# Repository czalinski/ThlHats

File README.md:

# ThlHats

Test devices in the Raspberry Pi HAT form factor: KiCad 10 PCB designs and
their firmware (PIC, ESP32, STM32).

## Design rules

- 2-layer boards, at most 100 × 100 mm
- Mount on standard Raspberry Pi M2.5 standoffs (58 × 49 mm hole pattern)
- All symbols, footprints and 3D models are kept in this repo under `lib/`.
  The KiCad projects do not use the stock or globally installed libraries.

## Requirements

- KiCad 10 (`kicad-cli` and the `pcbnew` Python module, run with the system `python3`)
- `pdftoppm` (poppler-utils), optional, for rendering schematics to images

## Quick start

```sh
# New 65 x 56.5 mm HAT with the 40-pin header, M2.5 holes, and a GND pour
tools/new_board.py my-board --title "My Board" --mcu esp32

# Bring parts into the repo libraries
tools/kilib.py symbol RF_Module:ESP32-S3-WROOM-1     # also copies footprint + 3D model
tools/kilib.py footprint Package_SO:SOIC-8_3.9x4.9mm_P1.27mm

# Parts from SnapEDA / Ultra Librarian / vendors
tools/kilib.py symbol PART --from ~/Downloads/PART.kicad_sym --lib Thl_Sensor --source "SnapEDA"
tools/kilib.py footprint PART_FP --from ~/Downloads/PART.kicad_mod --model ~/Downloads/PART.step \
    --lib Thl_Sensor --source "SnapEDA"

# Check (house rules + ERC + DRC) and produce fab files
tools/check_board.py boards/my-board
tools/fab.py boards/my-board
```

Open `boards/<name>/hardware/<name>.kicad_pro` in KiCad. Its project library
tables list only the libraries in `lib/`. After you add a new library, run
`tools/kilib.py sync`. The import commands do this for you.

## Layout

| Path | Contents |
|------|----------|
| `lib/` | Symbols, footprints, 3D models, and `SOURCES.md` (where each part came from) |
| `boards/<name>/hardware/` | KiCad project |
| `boards/<name>/firmware/` | Firmware for that board |
| `docs/` | Requirements (`docs/requirements.md`) |
| `tools/` | Board generator, library importer, symbol generator, checker, fab-output script |

## Library licensing

Parts copied from the KiCad libraries are CC-BY-SA 4.0 with the KiCad library
exception: boards made with them are not affected by the license. Parts from
other sources keep their own licenses, which are recorded in `lib/SOURCES.md`.

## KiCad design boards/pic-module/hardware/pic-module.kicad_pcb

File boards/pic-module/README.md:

# PIC32MK + power module (POC #1)

Plug-in module for the proof-of-concept boards (docs/requirements.md 4.0): the
can-controller's MCU and power entry, hand-soldered once and moved between POC
boards.

- Board: 56 x 74 mm, 2 layers, rev A. No mounting holes (`board.json`).
- U1 PIC32MK1024MCM064-I/PT (TQFP-64), 12 MHz crystal, decoupling, AVDD bead,
  MCLR network, ICSP (J2, PICkit/Snap pinout), debug UART (J5), heartbeat LED
  on RD8. Crystal Y1: Abracon ABM3-12.000MHZ-B2-T (12 MHz, 5.0 x 3.2 mm,
  CL 18 pF, ESR 60 ohm max, -20 to 70 C) with 27 pF C0G load caps; same part
  for the final board.
- Power entry copied from can-controller: J20 12 V in, F20 4 A, reverse-polarity
  P-FET Q1, TVS D31, TRACO TDN 5-2411WI (U20, isolated, 5 V 1 A), MCP1826S 3.3 V
  LDO (U2, 1 A).
- Two domains: RACK (+12V, GND_RACK) on the top strip, LOGIC (+5V, +3V3, GND,
  floating) below. U20 is the only crossing; a 2 mm copper-free gap separates
  them on both layers.

## Host interface

J3/J4 are 2 x 20, 2.54 mm sockets on the module's **bottom** (Sullins
PPTC202LFBN-RC, or any 2.54 mm stock); the host carries pin headers (Sullins
PRPC020DAAN-RC, or cut breakaway strip), via
the library part `Thl_Module:PIC32MK_Module` / footprint
`Thl_Module:PIC32MK_Module_Host` (origin = module top-left corner).

Keying:
1. J4 is placed so that a module turned 180 degrees lands 1.24 mm (half a pitch)
   off the host pins.
2. J3.9 is blocked on the module (glue a cut-off pin into that socket
   position); the host has no pin there. J3.10 is unused on both sides: it
   spaces the RACK pins from the LOGIC pins.

Pull pins 9 and 10 (row 5 of header A) out of the host's header before
soldering it; the host footprint has no pads there.

The pinout is generated: `hardware/module_pinout.py` matches the MCU pins to
header positions clockwise around the chip, so the module's fan-out has no
crossings. Host pin names are the PIC port names; a suffix says what the
module itself hangs on that pin:

- `RB5_PGD`, `RB6_PGC`: ICSP (J2). Keep host loads off them, or isolate them
  while programming.
- `RF1_TX`, `RC6_RX`: debug UART J5 (U1TX/U1RX by PPS).
- `RD8_LED`: heartbeat LED D2 (1 k to GND through the LED).
- `MCLR`: 10 k pull-up and 100 nF on the module; a host may add a reset button.
- `USB_DP`, `USB_DN`, `VBUS`: 100 k pull-downs on the module (USB unused unless
  a host wires a connector).

Supplies on the header: +12V x4 and GND_RACK x4 (J3.1-8, RACK, after the
input protection; a host may feed +12V here instead of using J20, without
protection), +5V x3, +3V3 x5, GND x11 (LOGIC). +5V is limited by U20 (1 A
total, of which the module uses about 0.1 A); +3V3 by U2 (1 A, mind the LDO's
dissipation: (5 - 3.3) V x I).

| J3 odd | J3 even | | J4 odd | J4 even |
|---|---|---|---|---|
| 1 +12V | 2 +12V | | 1 +5V | 2 GND |
| 3 +12V | 4 +12V | | 3 RG9 | 4 MCLR |
| 5 GND_RACK | 6 GND_RACK | | 5 RG8 | 6 RG7 |
| 7 GND_RACK | 8 GND_RACK | | 7 RG6 | 8 RB15 |
| 9 (key: no pin) | 10 (no pin) | | 9 +3V3 | 10 GND |
| 11 GND | 12 GND | | 11 RB14 | 12 RA7 |
| 13 RA12 | 14 RA11 | | 13 RA10 | 14 RB13 |
| 15 RA0 | 16 RA1 | | 15 RB12 | 16 RB11 |
| 17 RB0 | 18 RB1 | | 17 RB10 | 18 RF1_TX |
| 19 +3V3 | 20 GND | | 19 +3V3 | 20 GND |
| 21 RB2 | 22 RB3 | | 21 RF0 | 22 RC9 |
| 23 RC0 | 24 RC1 | | 23 RD6 | 24 RD5 |
| 25 RC2 | 26 RC11 | | 25 RC8 | 26 RC7 |
| 27 +5V | 28 GND | | 27 RC6_RX | 28 RB9 |
| 29 RE12 | 30 RE13 | | 29 +5V | 30 GND |
| 31 RE14 | 32 RE15 | | 31 RB8 | 32 RC13 |
| 33 RA8 | 34 RB4 | | 33 RB7 | 34 RC10 |
| 35 +3V3 | 36 GND | | 35 RB6_PGC | 36 RB5_PGD |
| 37 RA4 | 38 USB_DP | | 37 RD8_LED | 38 VBUS |
| 39 USB_DN | 40 GND | | 39 +3V3 | 40 GND |

## Changing the pinout

Edit `hardware/module_pinout.py`, then regenerate the module
(`gen_schematic.py`, `tools/sync_pcb.py`, `place.py`, reroute) and the host
part (`python3 lib/footprint_src/Thl_Module/pic_module.py` and
`tools/make_symbol.py lib/symbol_src/Thl_Module/PIC32MK_Module.csv`), and
update every host board.

## Build files

- `hardware/gen_schematic.py`: schematic (bootstrap; stop using it once the
  schematic is edited in KiCad).
- `hardware/place.py`: outline, placement, pours (GND both layers in LOGIC,
  GND_RACK / +12V in RACK, a +3V3 island under U1), isolation gap keep-outs
  (rerunnable; leaves tracks alone).
- `hardware/route.py`: pre-routing (not rerunnable): U1 VDD pins get inward
  stubs into the +3V3 island, VSS pins inward vias to the GND plane, every
  other SMD ground pad a fanout via.
- Autorouting: `tools/freeroute.py` (Freerouting 1.9.0 under xvfb, top layer
  preferred, bottom = GND plane), command in `route.py`'s docstring.
- Rev A was then finished by hand (2026-10-06): `miniroute.complete_net` for
  the last few nets, AVDD (U1.19) escaped inward to a via, RC11 kept on top
  past J3, `miniroute.stitch_pads` for header GND pins cut off from the pour,
  `tools/silk_tidy.py` for the references. Rerunning `place.py` is safe;
  rerunning `route.py`/the autorouter starts over and loses those fixes.
- U20 (TRACO: no traces under the converter) is enforced by a rule in
  `pic-module.kicad_dru`: only its own nets under its courtyard.
- Board setup accepts one thermal spoke (`min_resolved_spokes` 1): header GND
  pins between fan-out tracks often get only one.

## Open items

- Verify the Sullins socket/header MPNs (or use stock 2.54 mm parts) and the
  mated height against parts under the module on the host.
- No STEP models for U20 (TRACO TDN 5WI) and F20 (NANO2 fuse).

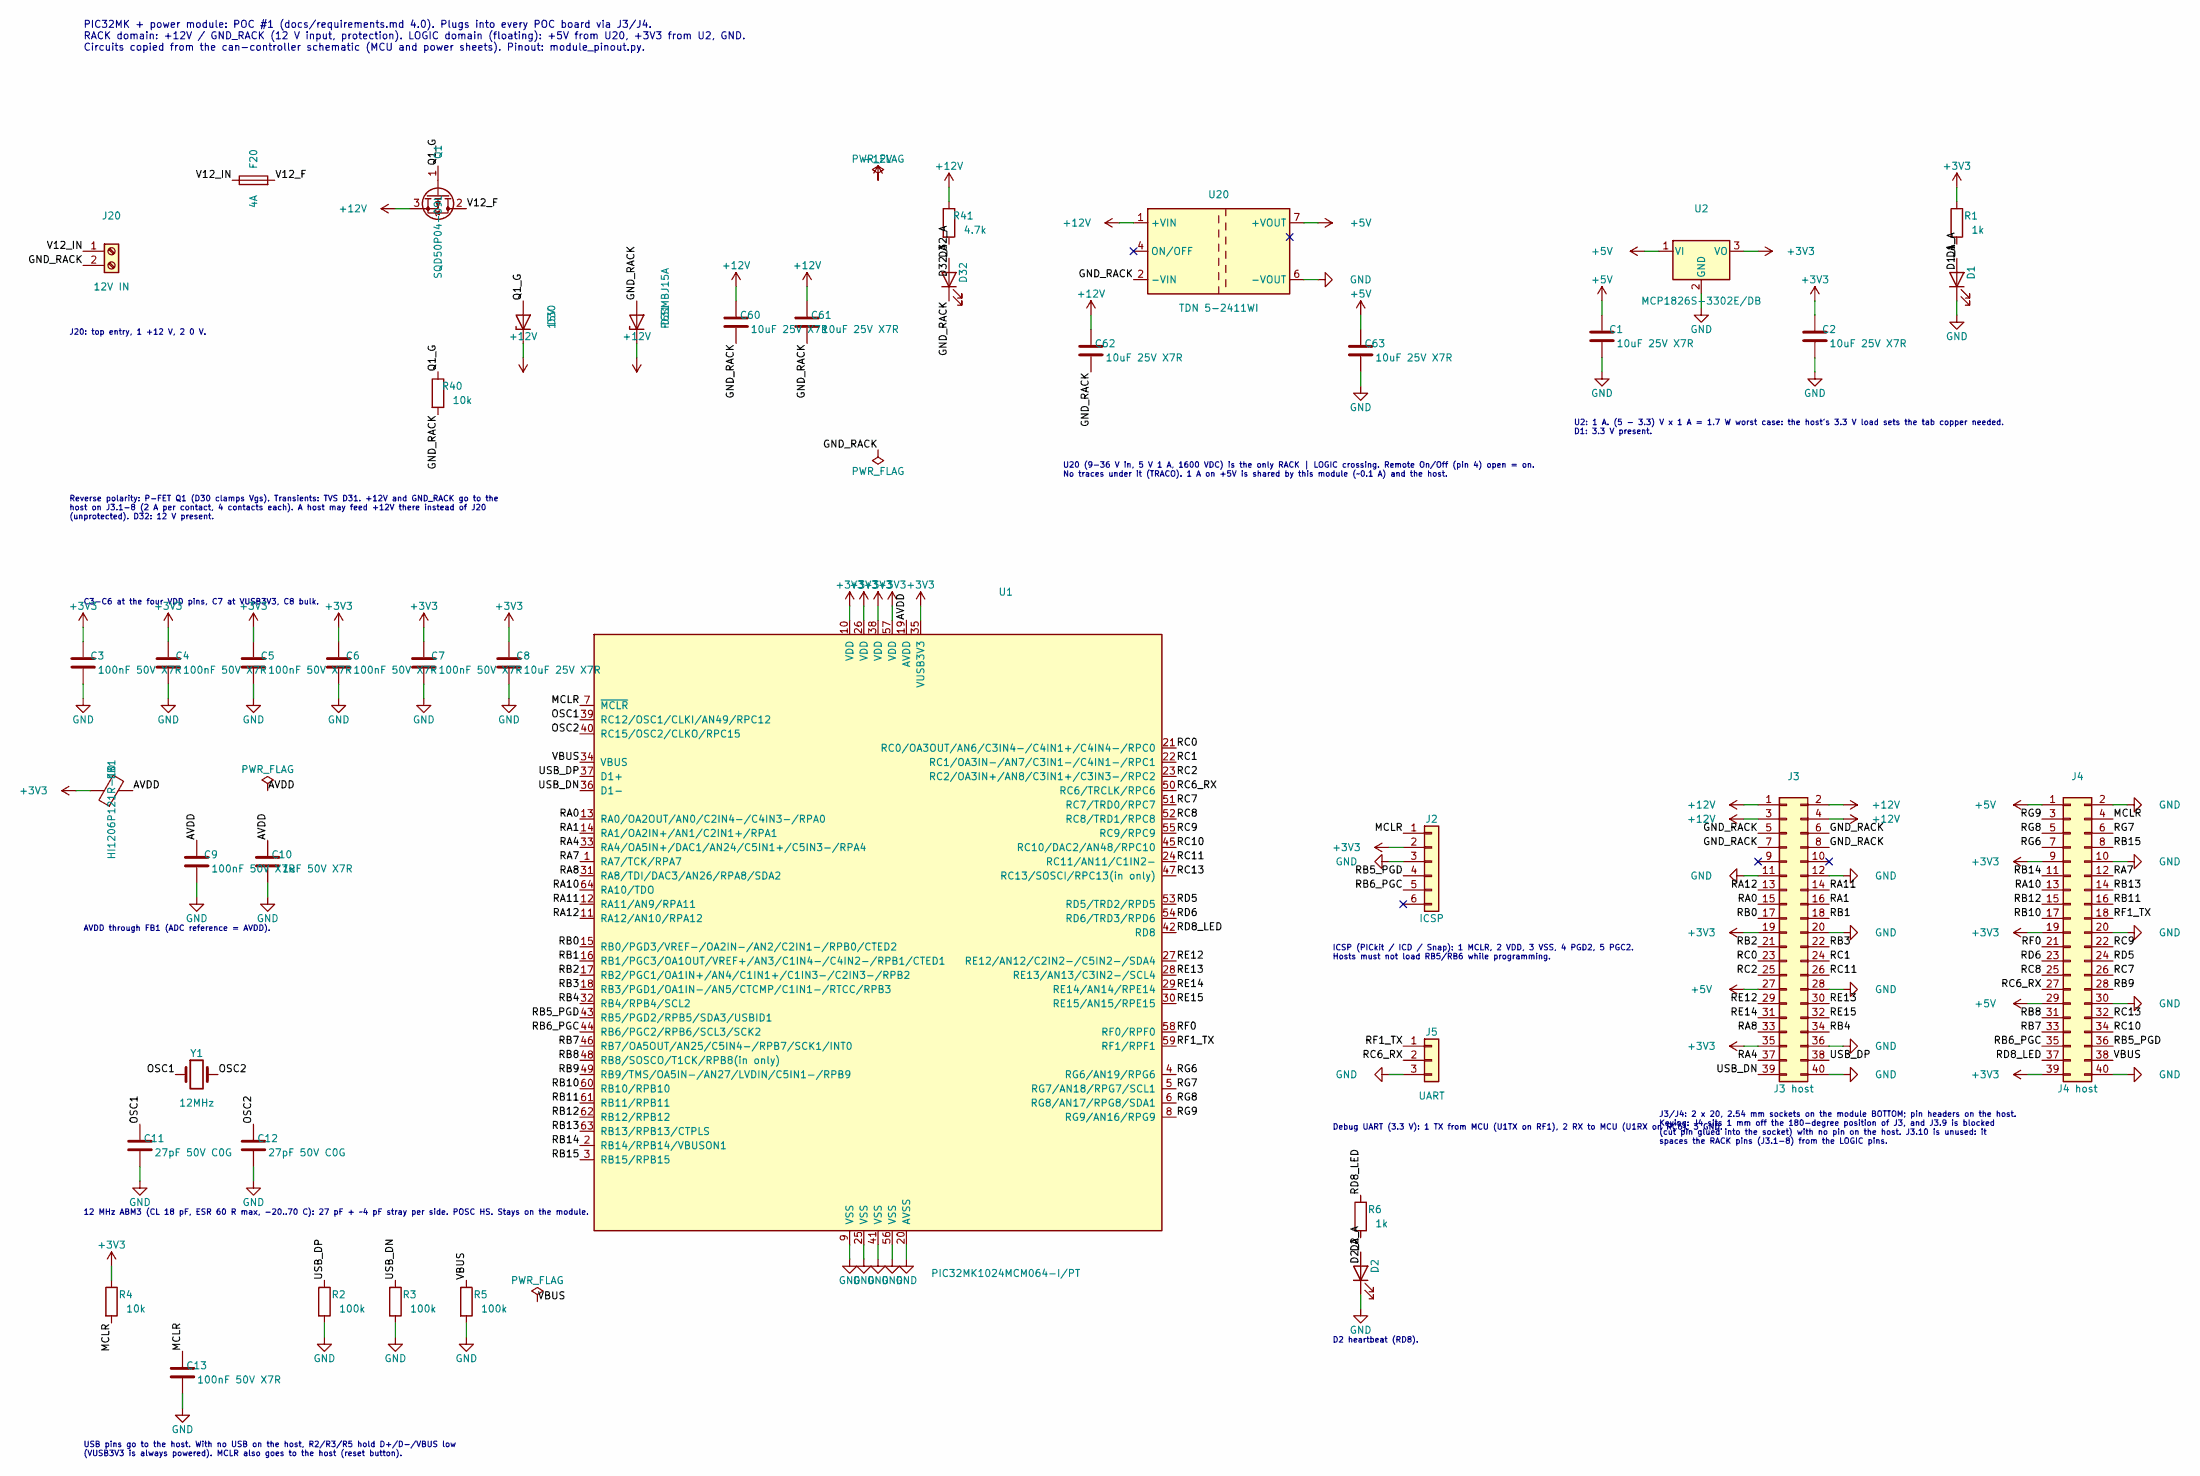
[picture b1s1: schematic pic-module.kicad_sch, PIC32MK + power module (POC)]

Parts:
C1, C2, C8, C60, C61, C62, C63: 10uF 25V X7R; C_1206_3216Metric_Pad1.33x1.80mm_HandSolder; MPN CL31B106KAHZW6E
C3, C4, C5, C6, C7, C9, C13: 100nF 50V X7R; C_0805_2012Metric_Pad1.18x1.45mm_HandSolder; MPN C0805C104K5RACTU
C10: 1uF 50V X7R; C_1206_3216Metric_Pad1.33x1.80mm_HandSolder; MPN C1206C105K5RACTU
C11, C12: 27pF 50V C0G; C_0805_2012Metric_Pad1.18x1.45mm_HandSolder; MPN C0805C270J5GACTU
D1, D2, D32: LED green; LED_1206_3216Metric_Pad1.42x1.75mm_HandSolder; MPN LTST-C150KGKT
D30: 15V; D_SOD-123; MPN BZT52C15-7-F
D31: P6SMBJ15A; D_SMB_Handsoldering; MPN P6SMBJ15A
F20: 4A; Fuse_Littelfuse-NANO2-451_453; MPN 0451004.MRL
FB1: HI1206P121R-10; L_1206_3216Metric_Pad1.22x1.90mm_HandSolder; MPN HI1206P121R-10
J2: ICSP; PinHeader_1x06_P2.54mm_Vertical; MPN TSW-106-07-G-S
J3: J3 host; PinSocket_2x20_P2.54mm_Vertical; MPN PPTC202LFBN-RC
J4: J4 host; PinSocket_2x20_P2.54mm_Vertical; MPN PPTC202LFBN-RC
J5: UART; PinHeader_1x03_P2.54mm_Vertical; MPN TSW-103-07-G-S
J20: 12V IN; PhoenixContact_MSTBVA_2,5_2-G-5,08_1x02_P5.08mm_Vertical; MPN 1755736
Q1: SQD50P04-09L; TO-252-2; MPN SQD50P04-09L_GE3
R1, R6: 1k; R_1206_3216Metric_Pad1.30x1.75mm_HandSolder; MPN RC1206FR-071KL
R2, R3, R5: 100k; R_1206_3216Metric_Pad1.30x1.75mm_HandSolder; MPN RC1206FR-07100KL
R4, R40: 10k; R_1206_3216Metric_Pad1.30x1.75mm_HandSolder; MPN RC1206FR-0710KL
R41: 4.7k; R_1206_3216Metric_Pad1.30x1.75mm_HandSolder; MPN RC1206FR-074K7L
U1: PIC32MK1024MCM064-I/PT; TQFP-64_10x10mm_P0.5mm; MPN PIC32MK1024MCM064-I/PT
U2: MCP1826S-3302E/DB; SOT-223-3_TabPin2; MPN MCP1826S-3302E/DB
U20: TDN 5-2411WI; Converter_DCDC_TRACO_TDN_5-xxxxWI_THT; MPN TDN 5-2411WI
Y1: 12MHz; Crystal_SMD_5032-2Pin_5.0x3.2mm_HandSoldering; MPN ABM3-12.000MHZ-B2-T

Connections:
+3V3: C2.1, C3.1, C4.1, C5.1, C6.1, C7.1, C8.1, FB1.1, J2.2, J3.19, J3.35, J4.9, J4.19, J4.39, R1.1, R4.1, U1.10 (VDD), U1.26 (VDD), U1.35 (VUSB3V3), U1.38 (VDD), U1.57 (VDD), U2.3 (VO)
+5V: C1.1, C63.1, J3.27, J4.1, J4.29, U2.1 (VI), U20.7 (+VOUT)
+12V: C60.1, C61.1, C62.1, D30.1 (K), D31.1 (K), J3.1, J3.2, J3.3, J3.4, Q1.3 (S), R41.1, U20.1 (+VIN)
/AVDD: C9.1, C10.1, FB1.2, U1.19 (AVDD)
/D1_A: D1.2 (A), R1.2
/D2_A: D2.2 (A), R6.2
/D32_A: D32.2 (A), R41.2
/GND_RACK: C60.2, C61.2, C62.2, D31.2 (A), D32.1 (K), J3.5, J3.6, J3.7, J3.8, J20.2, R40.2, U20.2 (-VIN)
/MCLR: C13.1, J2.1, J4.4, R4.2, U1.7 (~MCLR)
/OSC1: C11.1, U1.39 (RC12/OSC1/CLKI/AN49/RPC12), Y1.1
/OSC2: C12.1, U1.40 (RC15/OSC2/CLKO/RPC15), Y1.2
/Q1_G: D30.2 (A), Q1.1 (G), R40.1
/RA0: J3.15, U1.13 (RA0/OA2OUT/AN0/C2IN4-/C4IN3-/RPA0)
/RA1: J3.16, U1.14 (RA1/OA2IN+/AN1/C2IN1+/RPA1)
/RA4: J3.37, U1.33 (RA4/OA5IN+/DAC1/AN24/C5IN1+/C5IN3-/RPA4)
/RA7: J4.12, U1.1 (RA7/TCK/RPA7)
/RA8: J3.33, U1.31 (RA8/TDI/DAC3/AN26/RPA8/SDA2)
/RA10: J4.13, U1.64 (RA10/TDO)
/RA11: J3.14, U1.12 (RA11/AN9/RPA11)
/RA12: J3.13, U1.11 (RA12/AN10/RPA12)
/RB0: J3.17, U1.15 (RB0/PGD3/VREF-/OA2IN-/AN2/C2IN1-/RPB0/C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)
/RB1: J3.18, U1.16 (RB1/PGC3/OA1OUT/VREF+/AN3/C1IN4-/C4IN2-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)
/RB2: J3.21, U1.17 (RB2/PGC1/OA1IN+/AN4/C1IN1+/C1IN3-/C2IN3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)
/RB3: J3.22, U1.18 (RB3/PGD1/OA1IN-/AN5/CTCMP/C1IN1-/RTCC/R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)
/RB4: J3.34, U1.32 (RB4/RPB4/SCL2)
/RB5_PGD: J2.4, J4.36, U1.43 (RB5/PGD2/RPB5/SDA3/USBID1)
/RB6_PGC: J2.5, J4.35, U1.44 (RB6/PGC2/RPB6/SCL3/SCK2)
/RB7: J4.33, U1.46 (RB7/OA5OUT/AN25/C5IN4-/RPB7/SCK1/INT0)
/RB8: J4.31, U1.48 (RB8/SOSCO/T1CK/RPB8(in only))
/RB9: J4.28, U1.49 (RB9/TMS/OA5IN-/AN27/LVDIN/C5IN1-/RPB9)
/RB10: J4.17, U1.60 (RB10/RPB10)
/RB11: J4.16, U1.61 (RB11/RPB11)
/RB12: J4.15, U1.62 (RB12/RPB12)
/RB13: J4.14, U1.63 (RB13/RPB13/CTPLS)
/RB14: J4.11, U1.2 (RB14/RPB14/VBUSON1)
/RB15: J4.8, U1.3 (RB15/RPB15)
/RC0: J3.23, U1.21 (RC0/OA3OUT/AN6/C3IN4-/C4IN1+/C4IN4-/RPC0)
/RC1: J3.24, U1.22 (RC1/OA3IN-/AN7/C3IN1-/C4IN1-/RPC1)
/RC2: J3.25, U1.23 (RC2/OA3IN+/AN8/C3IN1+/C3IN3-/RPC2)
/RC6_RX: J4.27, J5.2, U1.50 (RC6/TRCLK/RPC6)
/RC7: J4.26, U1.51 (RC7/TRD0/RPC7)
/RC8: J4.25, U1.52 (RC8/TRD1/RPC8)
/RC9: J4.22, U1.55 (RC9/RPC9)
/RC10: J4.34, U1.45 (RC10/DAC2/AN48/RPC10)
/RC11: J3.26, U1.24 (RC11/AN11/C1IN2-)
/RC13: J4.32, U1.47 (RC13/SOSCI/RPC13(in only))
/RD5: J4.24, U1.53 (RD5/TRD2/RPD5)
/RD6: J4.23, U1.54 (RD6/TRD3/RPD6)
/RD8_LED: J4.37, R6.1, U1.42 (RD8)
/RE12: J3.29, U1.27 (RE12/AN12/C2IN2-/C5IN2-/SDA4)
/RE13: J3.30, U1.28 (RE13/AN13/C3IN2-/SCL4)
/RE14: J3.31, U1.29 (RE14/AN14/RPE14)
/RE15: J3.32, U1.30 (RE15/AN15/RPE15)
/RF0: J4.21, U1.58 (RF0/RPF0)
/RF1_TX: J4.18, J5.1, U1.59 (RF1/RPF1)
/RG6: J4.7, U1.4 (RG6/AN19/RPG6)
/RG7: J4.6, U1.5 (RG7/AN18/RPG7/SCL1)
/RG8: J4.5, U1.6 (RG8/AN17/RPG8/SDA1)
/RG9: J4.3, U1.8 (RG9/AN16/RPG9)
/USB_DN: J3.39, R3.1, U1.36 (D1-)
/USB_DP: J3.38, R2.1, U1.37 (D1+)
/V12_F: F20.2, Q1.2 (D)
/V12_IN: F20.1, J20.1
/VBUS: J4.38, R5.1, U1.34 (VBUS)
GND: C1.2, C2.2, C3.2, C4.2, C5.2, C6.2, C7.2, C8.2, C9.2, C10.2, C11.2, C12.2, C13.2, C63.2, D1.1 (K), D2.1 (K), J2.3, J3.11, J3.12, J3.20, J3.28, J3.36, J3.40, J4.2, J4.10, J4.20, J4.30, J4.40, J5.3, R2.2, R3.2, R5.2, U1.9 (VSS), U1.20 (AVSS), U1.25 (VSS), U1.41 (VSS), U1.56 (VSS), U2.2 (GND), U20.6 (-VOUT)

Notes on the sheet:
PIC32MK + power module: POC #1 (docs/requirements.md 4.0). Plugs into every POC board via J3/J4. RACK domain: +12V / GND_RACK (12 V input, protection). LOGIC domain (floating): +5V from U20, +3V3 from U2, GND. Circuits copied from the can-controller schematic (MCU and power sheets). Pinout: module_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
J20: top entry, 1 +12 V, 2 0 V.
Reverse polarity: P-FET Q1 (D30 clamps Vgs). Transients: TVS D31. +12V and GND_RACK go to the host on J3.1-8 (2 A per contact, 4 contacts each). A host may feed +12V there instead of J20 (unprotected). D32: 12 V present.
U20 (9-36 V in, 5 V 1 A, 1600 VDC) is the only RACK | LOGIC crossing. Remote On/Off (pin 4) open = on. No traces under it (TRACO). 1 A on +5V is shared by this module (~0.1 A) and the host.
U2: 1 A. (5 - 3.3) V x 1 A = 1.7 W worst case: the host's 3.3 V load sets the tab copper needed. D1: 3.3 V present.
C3-C6 at the four VDD pins, C7 at VUSB3V3, C8 bulk.
AVDD through FB1 (ADC reference = AVDD).
12 MHz ABM3 (CL 18 pF, ESR 60 R max, -20..70 C): 27 pF + ~4 pF stray per side. POSC HS. Stays on the module.
USB pins go to the host. With no USB on the host, R2/R3/R5 hold D+/D-/VBUS low (VUSB3V3 is always powered). MCLR also goes to the host (reset button).
ICSP (PICkit / ICD / Snap): 1 MCLR, 2 VDD, 3 VSS, 4 PGD2, 5 PGC2. Hosts must not load RB5/RB6 while programming.
Debug UART (3.3 V): 1 TX from MCU (U1TX on RF1), 2 RX to MCU (U1RX on RC6), 3 GND.
D2 heartbeat (RD8).
J3/J4: 2 x 20, 2.54 mm sockets on the module BOTTOM; pin headers on the host. Keying: J4 sits 1 mm off the 180-degree position of J3, and J3.9 is blocked (cut pin glued into the socket) with no pin on the host. J3.10 is unused: it spaces the RACK pins (J3.1-8) from the LOGIC pins.

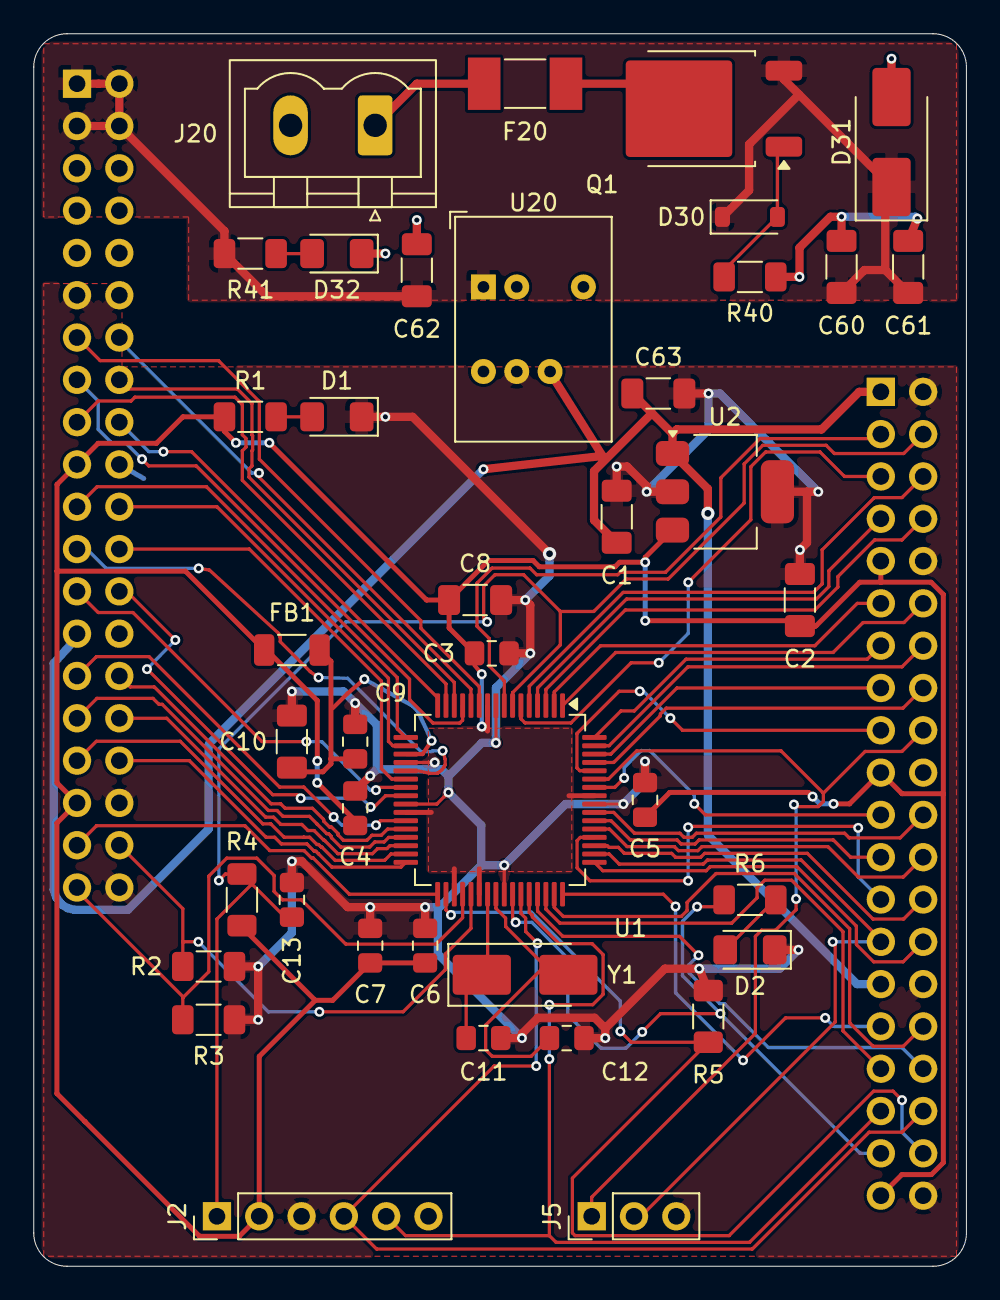
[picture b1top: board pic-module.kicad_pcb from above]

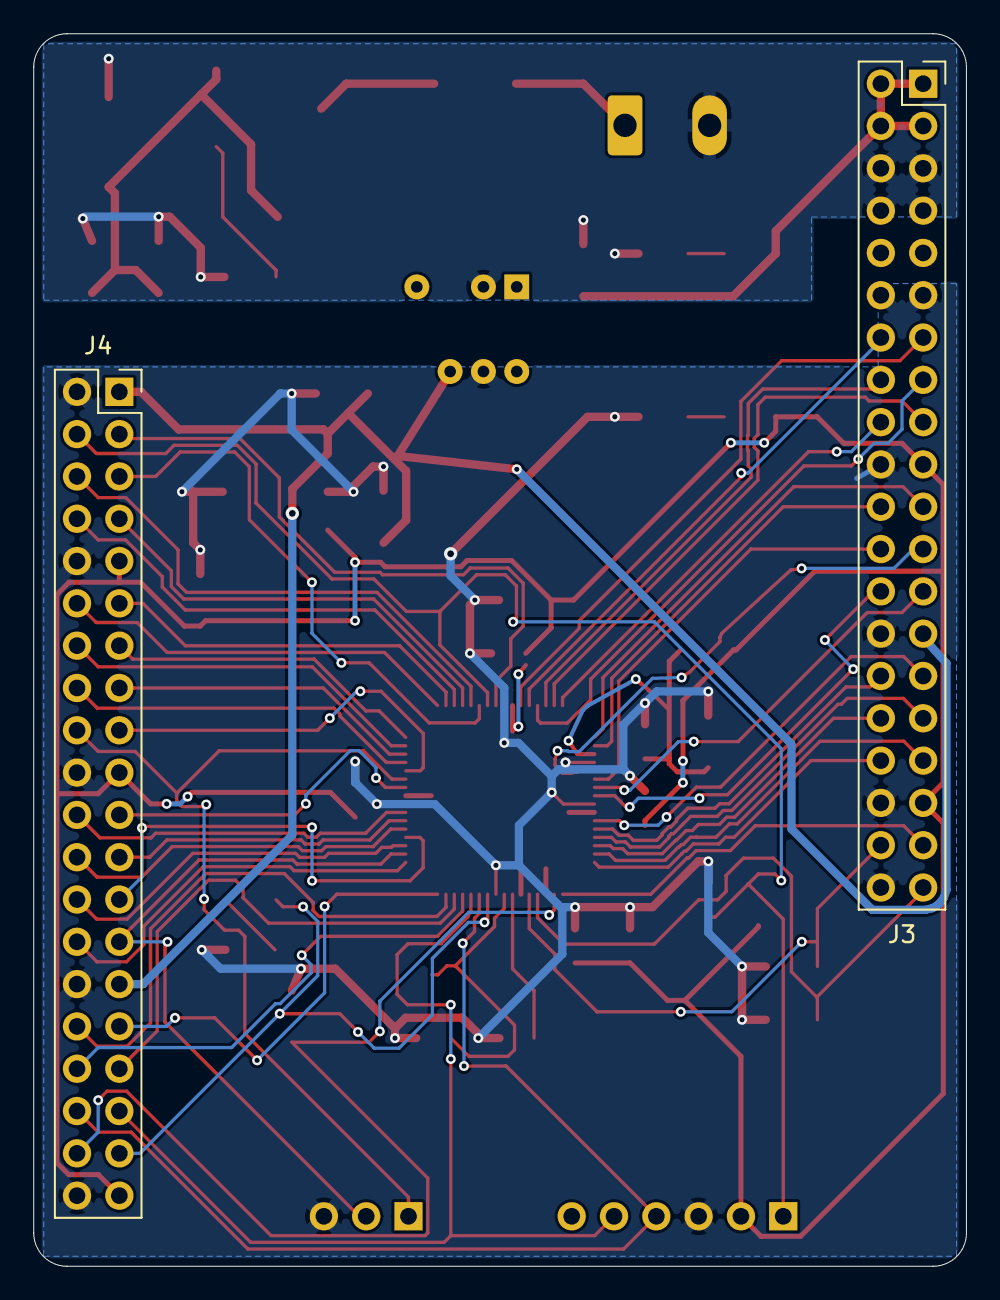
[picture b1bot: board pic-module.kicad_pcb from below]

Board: 2 copper layers, 56.0 x 74.0 mm, 42 parts (2 on the bottom side), 65 nets.

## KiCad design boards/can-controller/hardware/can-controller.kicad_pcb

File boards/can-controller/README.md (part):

# CAN Controller

Primary controller for the ThlHats HASS stack: four isolated CAN FD buses and
relay drive (the gaps the MCC HATs leave), plus a couple of GPIO and
high-voltage analog inputs so one card covers small jobs. Requirements:
[`docs/requirements.md`](../../docs/requirements.md), sections 3 and 4.1.

- Board: 100 x 100 mm, 2 layers, rev A
- Mounting: stack interface with can-ssr (requirements 4.4): 4 x M4 corner
  holes on a 91 x 91 mm square; base of a stack of up to 4 can-ssr. No Pi holes
- Host link: **Ethernet** (WIZnet W6100, user-space TCP/UDP sockets, no
  drivers or sudo on the host); a switch is assumed in the rack
- Power: one 12 V DIN supply; the logic runs from an isolated DC-DC
- MCU: PIC32MK1024MCM064-I/PT; firmware loads over the ICSP header

## Scope reduction (2026-10-06)

The rev 3 design (8 GPIO, 8 relays through ISO6740 isolators, a ULN2803A and
an MCP23008 expander, 4 AI on an MCP3428, 2 x 0-10 V AO with DAC, reference,
LM358B and a 13 V boost) had grown past the board's purpose. Cut: analog out
(MCC 152 / can-ssr cover it), the expander, the isolators and ULN, 24 V-tolerant
GPIO, and half of the GPIO, relay and AI channels. Later the same day: USB and
the Pi header gave way to Ethernet, and every CAN bus got its own isolation
(no assumptions about DUT grounds). The schematic, placement and routing in
the "Superseded" sections are from the old scope and will be redone;
`gen_schematic.py`, `place_board.py` and `place_rev3.py` describe it.

## Domains and functional blocks

| Block | Baseline parts | Domain |
|-------|----------------|--------|
| MCU | PIC32MK1024MCM064, 12 MHz crystal, ICSP header | LOGIC |
| Ethernet | W6100 + 25 MHz crystal, RJ45 with magnetics and LEDs (MPN TBD) | LOGIC (magnetics isolate the host) |
| CAN x4 (FD) | ISOW1044 each (isolated data and power), TVS, termination jumper, ferrite beads, 4-pin terminal | crosses LOGIC / CANn; each CANn floats |
| CAN1 power | POWERED jumpers: CAN1 ground to RACK 0 V, +12 V through a PTC to pin 4 | crosses RACK / CAN1 |
| 12 V input | Keyed terminal, fuse, reverse-polarity P-FET, TVS | RACK |
| Logic supply | Isolated DC-DC 12 V to 5 V, 5 W (TRACO TDN 5-2411WI), 3.3 V LDO | crosses RACK / LOGIC |
| Relay drive x4 | 2 x dual PhotoMOS (LED from a PIC32 pin), sources +12 V to a 12 V coil; flyback diode, LED, shared PTC | crosses LOGIC / RACK |
| GPIO x4 | PIC32 pins directly, 3.3 V, series R + ESD clamp, ground terminal per pin | LOGIC |
| Analog in x2 | differential, +-116 V per input; a 10M / 130k divider to VMID on each of AIn+ and AIn- (PIC32 OA5 follower), PIC32 12-bit ADC, firmware subtracts | LOGIC |

## Parts (draft, 2026-10-06)

| Function | Part | Package | Notes |
|---|---|---|---|
| MCU | PIC32MK1024MCM064-I/PT | TQFP-64 0.5 mm | 4 x CAN FD, ADC, op amps; OA5 on pins 33/46/49 for VMID |
| Crystal | 12 MHz, CL 18 pF | 5032 SMD | Abracon ABM3-12.000MHZ-B2-T (chosen 2026-10-06 on the PIC module) |
| Ethernet | WIZnet W6100 | LQFP-48 0.5 mm | IPv4/IPv6; not pin-compatible with the W5500 |
| Ethernet crystal | 25 MHz, CL 12 pF | SMD | MPN TBD; 8 pF load caps, 1 M across (WIZnet ref. V1.1) |
| W6100 support | RSET_BG 12k + 300R 1 %; TX/RX 2 x 49.9R + 0.1 uF to GND per pair at the chip; jack CT (P4) to 3V3A with 0.1 uF + 1 uF; 1V2O 3.3 uF; beads 3V3D->3V3A and 1V2D->1V2A (HI1206P121R-10); MOD[3:0] 10k pull-downs (SPI); LNKn/ACTn -> jack LEDs via 330R; shield 1 nF/2 kV to GND | 1206/0805 | WIZnet W6100_Ref_Schematic_V110_use_mag |
| RJ45 | Pulse JD0-0004NL, 1:1 magnetics, green/yellow LEDs, shielded | THT | `Thl_Connector:JD0-0004NL` / `RJ45_Pulse_JD0-0004NL_Horizontal` (from the datasheet). Pins 1/2 TX, 3/5 RX, 4 centre taps; 7-10 are PoE spare-pair pins, left unconnected; no 3D model (IGES only) |
| Ethernet supply filter | HI1206P121R-10 ferrite bead | 1206 | between the analog and digital 3.3 V supplies of the Ethernet chip (user's earlier design) |
| Logic supply | TRACO TDN 5-2411WI (5 W, 9-36 V in, 5 V 1 A, 1600 VDC) | DIP-8 | stock footprint Converter_DCDC_TRACO_TDN_5-xxxxWI_THT matches; Remote On/Off left open (on) |
| 3.3 V | MCP1826S-3302E/DB | SOT-223 | from the isolated 5 V |
| CAN transceiver x4 | TI ISOW1044 | DFM-20 (SOIC-20W footprint) | 5 kVrms, integrated isolated DC-DC, CAN FD 5 Mbit/s |
| CAN TVS x4 | NUP2105L | SOT-23 | |
| CAN termination x4 | 120R 1206 + 2-pin jumper | | |
| CAN1 power | PTC, hold >= 2 A, + POWERED jumpers | 1812/2920, 2.54 mm | up to 4 can-ssr at ~0.2 A each (estimate); CAN2-4: pin 4 not connected |
| Relay x4 | 2 x Panasonic AQW212 (2 Form A) | DIP-8 THT | 60 V, 0.5 A/ch, 2.5 R max, 1.5 kVrms; drive the LED at about 5 mA |
| Relay flyback x4 | 1N4148W / S1G class | SOD-123 / SMA | OUTn to 0 V |
| Relay feed | PTC | 1812 | shared by the 4 outputs |
| 12 V input | MSTBVA 2,5/2-G-5,08, fuse, P-FET reverse polarity, P6SMBJ15A TVS | | |
| GPIO x4 | series R 1206 + ESD clamp | | 3.3 V only |
| AI dividers x4 (2 per channel) | 10M + 130k 1206, 0.1 uF, BAT54S clamp per leg | | 10M needs a voltage-rated 1206 (or two in series); matching sets common-mode rejection |
| VMID | 3.3 V divider + PIC32MK OA5 follower | | also sampled by the ADC (AN25) |
| Connectors | MC 1,5/4-G-3,5 (CAN); SPTD double-level push-in (relay, GPIO, AI) | THT | |
| LEDs | 1206 | | power, heartbeat, CAN x4, relay x4 (Ethernet LEDs in the jack) |

## Floorplan (rev 6, 2026-10-06)

`hardware/floorplan_rev6.py OUT_DIR` draws it (real footprints for the edge
connectors and large parts, Dwgs.User block areas and standoff keep-outs,
Cmts.User domain boundaries) into a scratch board and renders the PNG; the
placement script will reuse its coordinates. Board corner at (100, 100) mm;
coordinates below are from the corner.

| Edge | Connector | Position | Domain |
|------|-----------|----------|--------|
| Left | CAN1 (J11) at the **stack CAN position** (pin 1 at y 15.5), under each can-ssr's CAN IN/OUT | y 12.45-29.05 | CAN1 |
| Left | RELAY (J30), SPTD 2x4: OUT1-4 / 0 V | y 33-49.6 | RACK |
| Left | 12 V IN (J20), MSTBVA 2,5/2-G-5,08, top entry | y 56-69 | RACK |
| Right | CAN4, CAN3, CAN2 (J14-J12), 2 mm island gaps | y 22-75.8 | CANn |
| Top | RJ45 (J4) | x 40-59 | LOGIC |
| Bottom | I/O (J40), SPTD 2x6: GPIO1-4 / GND, AI1-2 + / - | x 45-68.6 | LOGIC |

- 100 x 100 mm stack interface: M4 standoff holes 4.5 mm in from each corner
  (91 x 91 mm), `Thl_Mechanical:MountingHole_4.3mm_M4_Standoff7mm` (4.3 mm courtyard).
- CAN1 island top-left (x < 24, y < 30): its ISOW1044 (rotated, logic side
  facing in) straddles x = 24; the POWERED jumpers straddle y = 30 into RACK.
- RACK on the left below CAN1 (x < 33, y 30-90): the PhotoMOS pair and the
  TDN 5 DC-DC straddle x = 33.
- CAN2-CAN4 islands on the right (x > 75): ISOW1044s straddle x = 75, centred
  on their connectors (no stepping needed at this pitch).
- LOGIC in the middle: W6100 under the RJ45, MCU at (55, 50), GPIO/AI parts
  above J40, CAN LEDs beside the right-hand isolators, ICSP header top right.
- Much more room than rev 5: logic routing and the CAN bus zones are no longer
  tight.

## Schematic (generated 2026-10-06, new scope)

`hardware/gen_schematic.py` writes the root sheet and six block sheets: MCU and
logic power, Ethernet (W6100), CAN x4 (ISOW1044), 12 V input and isolated logic
supply, relay drive (AQW212), GPIO and differential analog in. It is for the
initial capture only: once the schematic is edited in KiCad, stop running it.
ERC: 0 violations. A netlist check confirms no net crosses a domain except at
the designed crossings (TDN 5-2411WI, ISOW1044, AQW212, CAN1 POWERED jumpers;
the Ethernet shield couples to logic GND through 1 nF / 2 kV only).

MCU pin map (PPS groups checked against DS60001519E Tables 13-1/13-2):
CAN1 RB2/RB3 (17/18), CAN2 RA1/RB0 (14/15), CAN3 RC0/RC1 (21/22), CAN4
RE15/RA8 (30/31); W6100 on SPI3: SCK3 RC9 (55), SDO3 RC8 (52), SDI3 RC7 (51),
CS RD5 (53), INT RD6 (54), RST RF0 (58); UART1 TX RF1 (59), RX RC6 (50);
OA5 follower IN+ RA4 (33), IN- RB9 (49), OUT RB7 (46) = VMID = AN25; AI1+/-
AN12/AN13 (27/28), AI2+/- AN11/AN8 (24/23); GPIO1-4 RB10-RB13 (60-63); relay
drives RB14, RB15, RG6, RG7 (2-5); CAN LEDs RG8, RG9, RA12, RA11 (6, 8, 11,
12); heartbeat RD8 (42); ICSP PGx2 (43/44). USB unused: VUSB3V3 to VDD, VBUS to
VSS, D+/D- 10k to VSS. Firmware: disable JTAG, ICESEL = PGx2, drive unused pins low.

Still TBD in the schematic: the 25 MHz crystal (CL 12 pF; the 12 MHz is
Abracon ABM3-12.000MHZ-B2-T, to enter on the next schematic edit)
and the W6100 load caps and 3.3 uF 1V2O capacitor MPNs; the ISOW1044 beads
(BLM31KN102SN1L entered) to be checked against TI's layout guide.

## Placement (first pass, floorplan rev 6, 2026-10-06)

The rev 3 layout was cleared (footprints, tracks, zones, drawings); the board
keeps its setup and net classes. New outline 100 x 100 mm with the four M4
standoff holes, then `tools/sync_pcb.py` and `hardware/place_rev6.py` (run
once; after hand edits in KiCad, don't rerun). Fixed parts at the floorplan
positions; the rest placed near the pins they serve, each inside its domain
(domain boundaries pulled back 1 mm, so every isolation gap is >= 2 mm).

- Changes from the floorplan drawing: the LOGIC | CAN2-4 boundary moved from
  x = 75 to x = 73 (the CAN3 island was too small for its parts); U10 up 1 mm
  and J30 down 1.5 mm to fit the CAN1 POWERED jumpers; J40 at x 34-57.6 with
  the AI dividers to its right; MCU rotated 90 degrees so pins 17-32 (CAN,
  AI) face the right-hand isolators.
- Relay flyback diodes are 1N4148W (SOD-123, 300 mA); coil currents are about
  100 mA at most.
- Checker: ERC clean, no courtyard overlaps or clearance errors, schematic
  parity clean; 438 unrouted connections; silkscreen cleanup still to do.

## Layout rules

- Connectors on any edge (no Pi header since 2026-10-06).
- Six copper domains (RACK, LOGIC, CAN1-CAN4); only the crossing parts bridge the gaps.

## Directories

- `hardware/` KiCad project
- `firmware/` firmware sources

## Superseded: floorplan (rev 2, variant B, 2026-10-05)

Drawn on the `Dwgs.User` layer of the PCB. Board corner at (100, 100) mm. The
board sits at the **top of the stack** (MCC HATs below), so top-entry
connectors and the area inside the HAT outline stay reachable.

| Edge | Connector (top/left first) | Length | Domain |
|------|---------------------------|--------|--------|
| Right | USB-C, GCT USB4085 (through-hole, USB 2.0) | 10 mm | logic |
| Right | CAN4, CAN3, CAN1, CAN2: Phoenix MC 1,5/4-G-3,5 (as can-ssr) | 4 x 17 mm | 12 V |
| Bottom | ANALOG: AI1-4 + 4 GND, AO1-2 + 2 GND, MC 1,5/12-G-3,5 | 45 mm | logic |
| Bottom | RELAY 1-8 + 12 V COM, MC 1,5/9-G-3,5 | 34 mm | 12 V |
| Left (below MH3) | GPIO 1-4 + 4 GND, MC 1,5/8-G-3,5 | 31 mm | logic |
| Left (MH1-MH3) | GPIO 5-8 + 4 GND, MC 1,5/8-G-3,5 | 31 mm | logic |
| Inboard | 12 V IN, top entry, Phoenix MSTBVA 2,5/2-G-5,08 | | 12 V |

- Mounting: the four Pi holes (MH1-MH4), plus M2.5 holes in the other three
  corners (MH5-MH7, a 93 x 93 mm square with MH1) for standoffs when the board
  is mounted on its own, e.g. on a second stack fed by a ribbon cable. No DIN
  clip holes (removed 2026-10-05): a 3D-printed adapter carries the DIN clip.
- One connector family (Phoenix MC 3.5) for all signals; the 12 V input uses a
  5.08 mm MSTB so it cannot take a signal plug. Pin counts differ by function
  (CAN 4, GPIO 8, relay 9, analog 12). A smaller plug can still go into a larger
  header, so every pin is designed to survive what a wrong plug could put on
  it: CAN cable 12 V on GPIO (24 V rated) and AO (protected), CAN lines into
  the ULN2803A outputs (harmless).
- 12 V domain: a strip x > 170 mm under the USB-C (the four CAN channels) plus
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
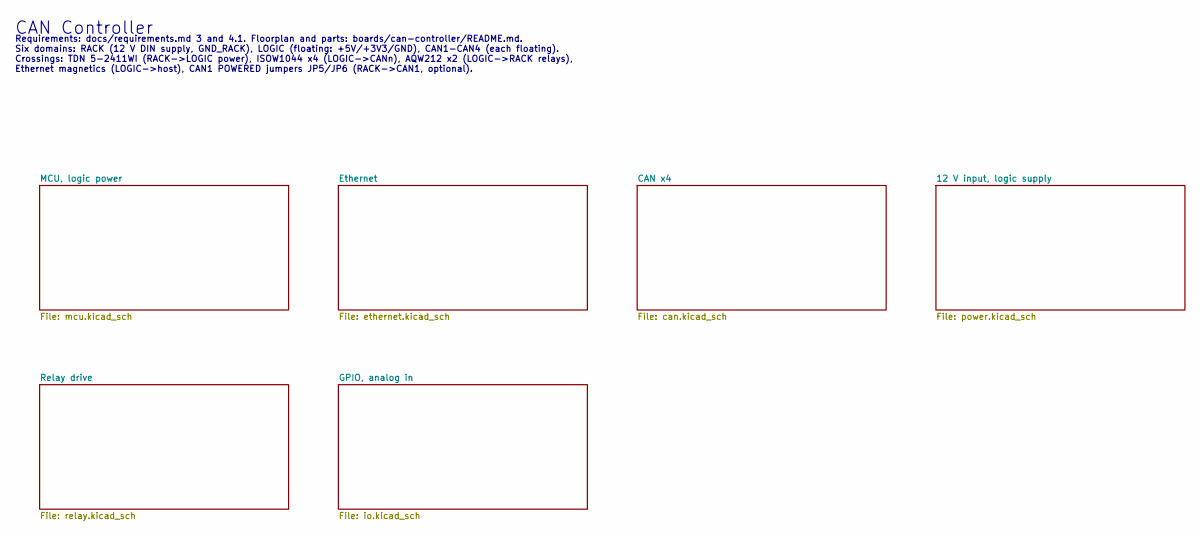
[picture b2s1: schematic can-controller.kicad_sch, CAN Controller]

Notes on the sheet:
CAN Controller
Requirements: docs/requirements.md 3 and 4.1. Floorplan and parts: boards/can-controller/README.md. Six domains: RACK (12 V DIN supply, GND_RACK), LOGIC (floating: +5V/+3V3/GND), CAN1-CAN4 (each floating). Crossings: TDN 5-2411WI (RACK->LOGIC power), ISOW1044 x4 (LOGIC->CANn), AQW212 x2 (LOGIC->RAC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

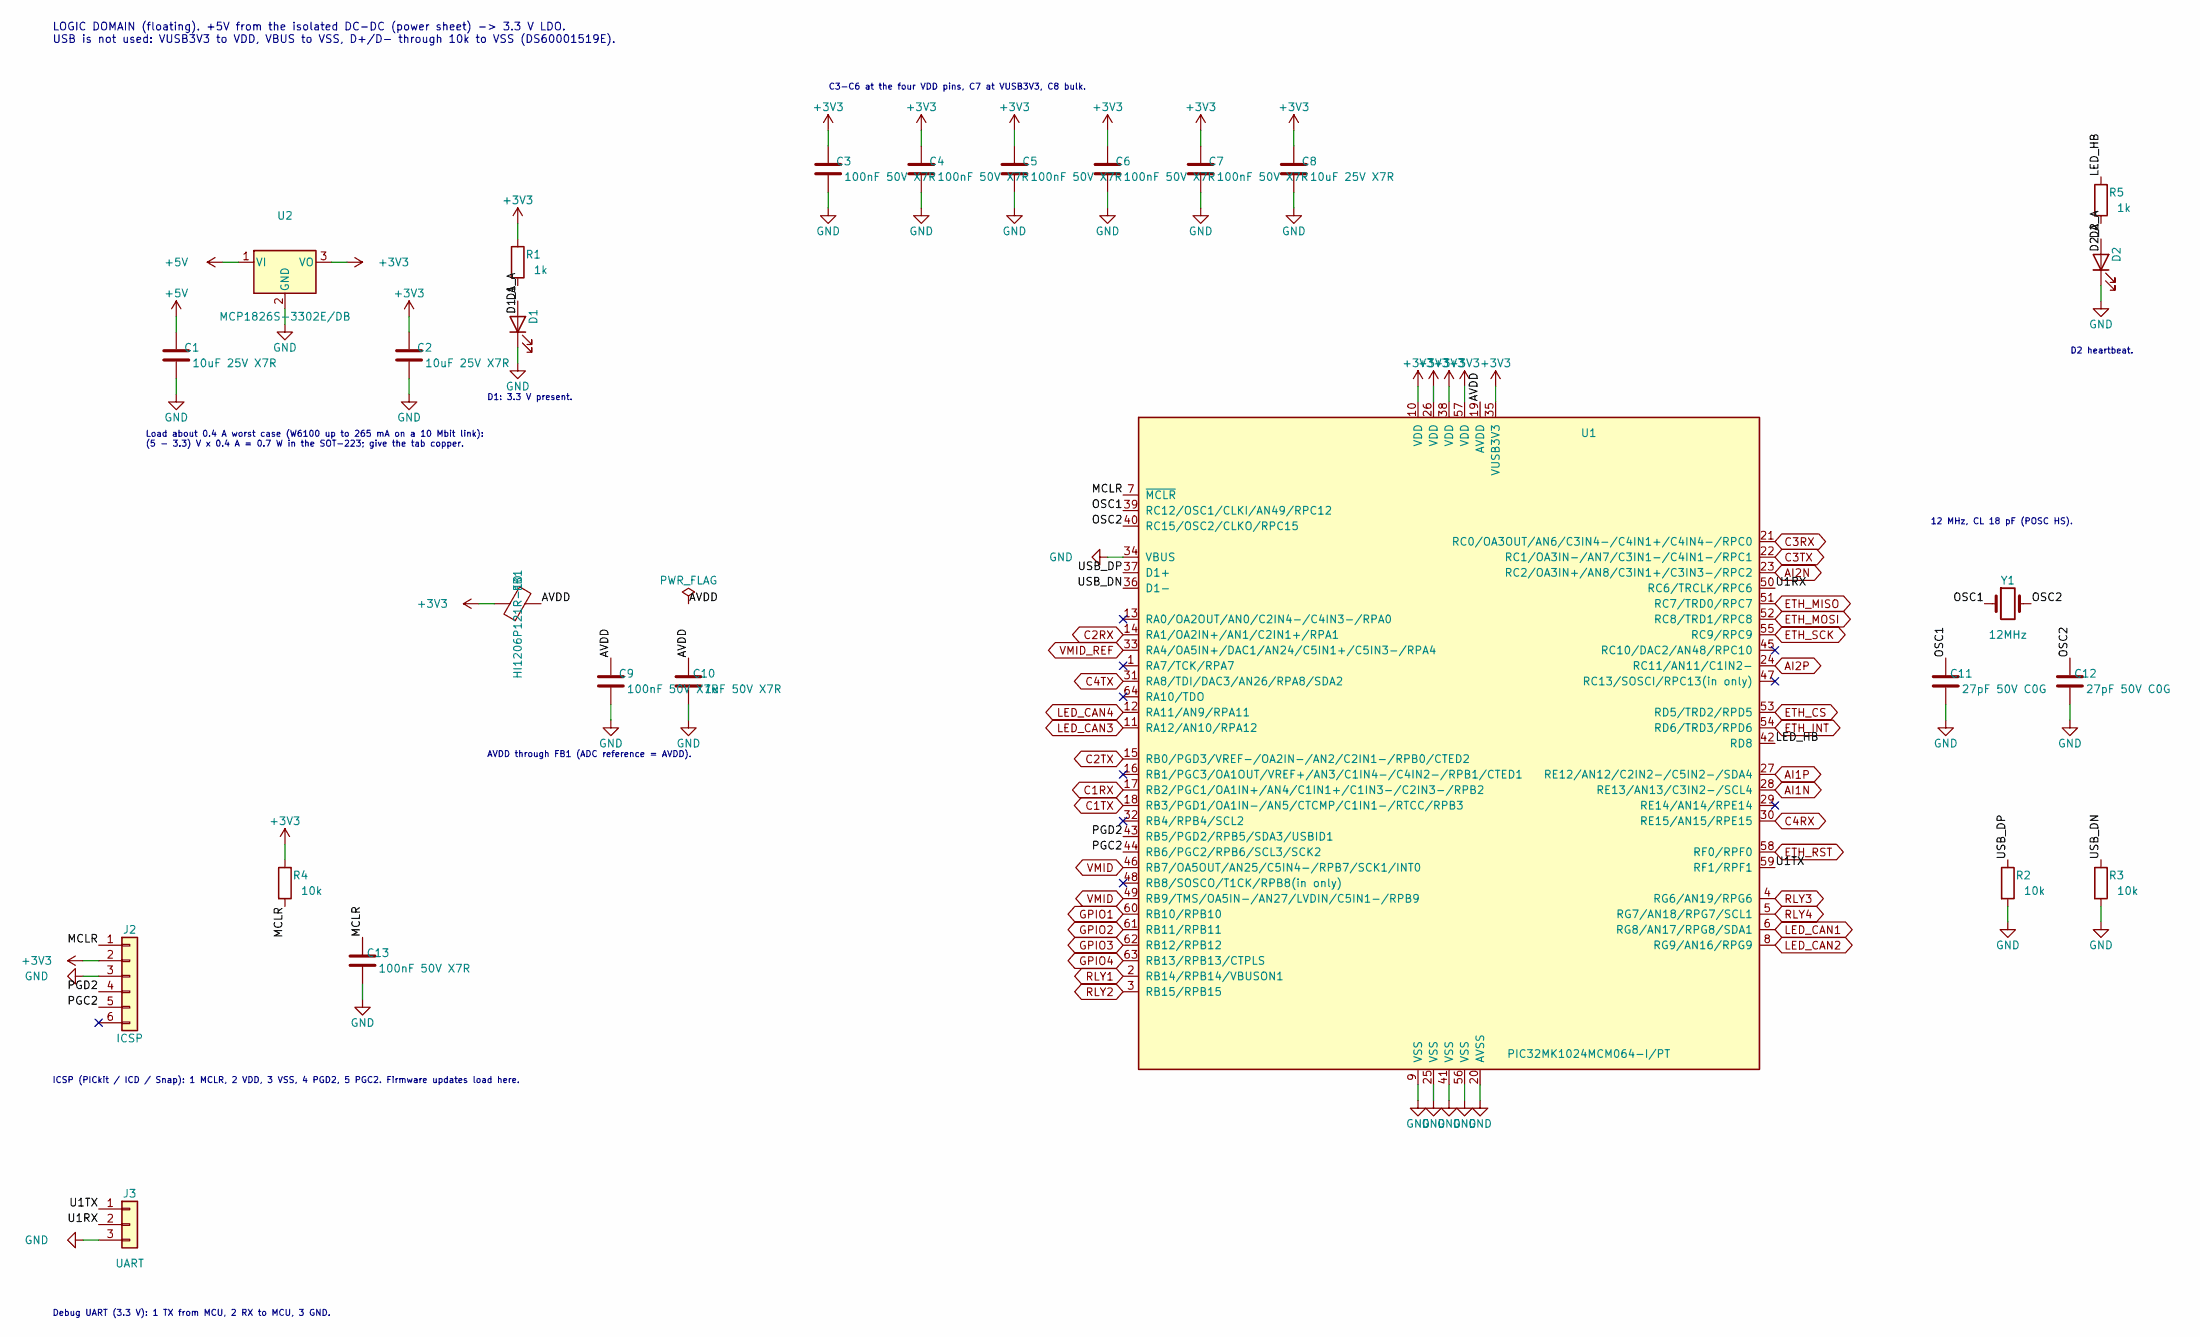
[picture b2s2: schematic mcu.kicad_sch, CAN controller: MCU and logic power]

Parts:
C1, C2, C8: 10uF 25V X7R; C_1206_3216Metric_Pad1.33x1.80mm_HandSolder; MPN CL31B106KAHZW6E
C3, C4, C5, C6, C7, C9, C13: 100nF 50V X7R; C_0805_2012Metric_Pad1.18x1.45mm_HandSolder; MPN C0805C104K5RACTU
C10: 1uF 50V X7R; C_1206_3216Metric_Pad1.33x1.80mm_HandSolder; MPN C1206C105K5RACTU
C11, C12: 27pF 50V C0G; C_0805_2012Metric_Pad1.18x1.45mm_HandSolder; MPN C0805C270J5GACTU
D1, D2: LED green; LED_1206_3216Metric_Pad1.42x1.75mm_HandSolder; MPN LTST-C150KGKT
FB1: HI1206P121R-10; L_1206_3216Metric_Pad1.22x1.90mm_HandSolder; MPN HI1206P121R-10
J2: ICSP; PinHeader_1x06_P2.54mm_Vertical; MPN TSW-106-07-G-S
J3: UART; PinHeader_1x03_P2.54mm_Vertical; MPN TSW-103-07-G-S
R1, R5: 1k; R_1206_3216Metric_Pad1.30x1.75mm_HandSolder; MPN RC1206FR-071KL
R2, R3, R4: 10k; R_1206_3216Metric_Pad1.30x1.75mm_HandSolder; MPN RC1206FR-0710KL
U1: PIC32MK1024MCM064-I/PT; TQFP-64_10x10mm_P0.5mm; MPN PIC32MK1024MCM064-I/PT
U2: MCP1826S-3302E/DB; SOT-223-3_TabPin2; MPN MCP1826S-3302E/DB
Y1: 12MHz; Crystal_SMD_5032-2Pin_5.0x3.2mm_HandSoldering; MPN TBD (12 MHz, 5032, CL 18 pF)

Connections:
+3V3: C2.1, C3.1, C4.1, C5.1, C6.1, C7.1, C8.1, FB1.1, J2.2, R1.1, R4.1, U1.10 (VDD), U1.26 (VDD), U1.35 (VUSB3V3), U1.38 (VDD), U1.57 (VDD), U2.3 (VO); also elsewhere on the board
+5V: C1.1, U2.1 (VI); also elsewhere on the board
/MCU, logic power/AVDD: C9.1, C10.1, FB1.2, U1.19 (AVDD)
/MCU, logic power/D1_A: D1.2 (A), R1.2
/MCU, logic power/D2_A: D2.2 (A), R5.2
/MCU, logic power/LED_HB: R5.1, U1.42 (RD8)
/MCU, logic power/MCLR: C13.1, J2.1, R4.2, U1.7 (~MCLR)
/MCU, logic power/OSC1: C11.1, U1.39 (RC12/OSC1/CLKI/AN49/RPC12), Y1.1
/MCU, logic power/OSC2: C12.1, U1.40 (RC15/OSC2/CLKO/RPC15), Y1.2
/MCU, logic power/PGC2: J2.5, U1.44 (RB6/PGC2/RPB6/SCL3/SCK2)
/MCU, logic power/PGD2: J2.4, U1.43 (RB5/PGD2/RPB5/SDA3/USBID1)
/MCU, logic power/U1RX: J3.2, U1.50 (RC6/TRCLK/RPC6)
/MCU, logic power/U1TX: J3.1, U1.59 (RF1/RPF1)
/MCU, logic power/USB_DN: R3.1, U1.36 (D1-)
/MCU, logic power/USB_DP: R2.1, U1.37 (D1+)
AI1N: U1.28 (RE13/AN13/C3IN2-/SCL4); also elsewhere on the board
AI1P: U1.27 (RE12/AN12/C2IN2-/C5IN2-/SDA4); also elsewhere on the board
AI2N: U1.23 (RC2/OA3IN+/AN8/C3IN1+/C3IN3-/RPC2); also elsewhere on the board
AI2P: U1.24 (RC11/AN11/C1IN2-); also elsewhere on the board
C1RX: U1.17 (RB2/PGC1/OA1IN+/AN4/C1IN1+/C1IN3-/C2IN3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); also elsewhere on the board
C1TX: U1.18 (RB3/PGD1/OA1IN-/AN5/CTCMP/C1IN1-/RTCC/R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); also elsewhere on the board
C2RX: U1.14 (RA1/OA2IN+/AN1/C2IN1+/RPA1); also elsewhere on the board
C2TX: U1.15 (RB0/PGD3/VREF-/OA2IN-/AN2/C2IN1-/RPB0/C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); also elsewhere on the board
C3RX: U1.21 (RC0/OA3OUT/AN6/C3IN4-/C4IN1+/C4IN4-/RPC0); also elsewhere on the board
C3TX: U1.22 (RC1/OA3IN-/AN7/C3IN1-/C4IN1-/RPC1); also elsewhere on the board
C4RX: U1.30 (RE15/AN15/RPE15); also elsewhere on the board
C4TX: U1.31 (RA8/TDI/DAC3/AN26/RPA8/SDA2); also elsewhere on the board
ETH_CS: U1.53 (RD5/TRD2/RPD5); also elsewhere on the board
ETH_INT: U1.54 (RD6/TRD3/RPD6); also elsewhere on the board
ETH_MISO: U1.51 (RC7/TRD0/RPC7); also elsewhere on the board
ETH_MOSI: U1.52 (RC8/TRD1/RPC8); also elsewhere on the board
ETH_RST: U1.58 (RF0/RPF0); also elsewhere on the board
ETH_SCK: U1.55 (RC9/RPC9); also elsewhere on the board
GND: C1.2, C2.2, C3.2, C4.2, C5.2, C6.2, C7.2, C8.2, C9.2, C10.2, C11.2, C12.2, C13.2, D1.1 (K), D2.1 (K), J2.3, J3.3, R2.2, R3.2, U1.9 (VSS), U1.20 (AVSS), U1.25 (VSS), U1.34 (VBUS), U1.41 (VSS), U1.56 (VSS), U2.2 (GND); also elsewhere on the board
GPIO1: U1.60 (RB10/RPB10); also elsewhere on the board
GPIO2: U1.61 (RB11/RPB11); also elsewhere on the board
GPIO3: U1.62 (RB12/RPB12); also elsewhere on the board
GPIO4: U1.63 (RB13/RPB13/CTPLS); also elsewhere on the board
LED_CAN1: U1.6 (RG8/AN17/RPG8/SDA1); also elsewhere on the board
LED_CAN2: U1.8 (RG9/AN16/RPG9); also elsewhere on the board
LED_CAN3: U1.11 (RA12/AN10/RPA12); also elsewhere on the board
LED_CAN4: U1.12 (RA11/AN9/RPA11); also elsewhere on the board
RLY1: U1.2 (RB14/RPB14/VBUSON1); also elsewhere on the board
RLY2: U1.3 (RB15/RPB15); also elsewhere on the board
RLY3: U1.4 (RG6/AN19/RPG6); also elsewhere on the board
RLY4: U1.5 (RG7/AN18/RPG7/SCL1); also elsewhere on the board
VMID: U1.46 (RB7/OA5OUT/AN25/C5IN4-/RPB7/SCK1/INT0), U1.49 (RB9/TMS/OA5IN-/AN27/LVDIN/C5IN1-/RPB9); also elsewhere on the board
VMID_REF: U1.33 (RA4/OA5IN+/DAC1/AN24/C5IN1+/C5IN3-/RPA4); also elsewhere on the board

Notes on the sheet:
LOGIC DOMAIN (floating). +5V from the isolated DC-DC (power sheet) -> 3.3 V LDO. USB is not used: VUSB3V3 to VDD, VBUS to VSS, D+/D- through 10k to VSS (DS60001519E).
Load about 0.4 A worst case (W6100 up to 265 mA on a 10 Mbit link): (5 - 3.3) V x 0.4 A = 0.7 W in the SOT-223; give the tab copper.
D1: 3.3 V present.
C3-C6 at the four VDD pins, C7 at VUSB3V3, C8 bulk.
AVDD through FB1 (ADC reference = AVDD).
12 MHz, CL 18 pF (POSC HS).
ICSP (PICkit / ICD / Snap): 1 MCLR, 2 VDD, 3 VSS, 4 PGD2, 5 PGC2. Firmware updates load here.
Debug UART (3.3 V): 1 TX from MCU, 2 RX to MCU, 3 GND.
D2 heartbeat.
